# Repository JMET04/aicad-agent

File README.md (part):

# aicad-agent 1.18.0

> 当前1.18.0是待审阅的发布候选，不是已发布的稳定Release。独立插件包验证与220项测试（218通过、2跳过）已通过；全仓历史项目测试仍有证据哈希与可选CAD依赖问题。不要把以下正式版本安装步骤当成已发行的证明。

一个面向 Agent 的确定性 CAD 约束、审查与修改插件。你可以直接用自然语言告诉 Codex 要画什么、参考什么、哪些尺寸必须准确；插件负责把要求转换为逐实体计划、数学约束、CAD 文件、交互修改器和可审计验证结果。

**默认不需要 API Key。** 当前 Codex Agent 负责理解任务，本地插件负责约束验证、编译、审查和宿主适配。

v1.18.0新增[整套成本与可用性采购前检查](agent-plugin/aicad-agent/docs/PROCUREMENT_PREFLIGHT.md)：免费裸PCB不等于整套免费，完整成本/供货/功能证据/明确预算未闭合时不能推进制造；检查通过也不是采购或实机授权。见[事故复盘与电脑复查结果](docs/procurement-incident-20261009.md)。

## 产品介绍

`aicad-agent` 是安装在 Codex 中的本地工程流水线：它先冻结领域、交付阶段、标准和输入权威顺序，再生成带稳定 ID、用途、依赖和数学约束的 CAD/EDA 候选，最后交付可点击修改器、中文审计、机器验证和 SHA-256 文件清单。它面向需要“可编辑、可复核、可追溯”结果的设计与工程流程，而不是只输出一张看起来相似的图片。

产品覆盖通用 2D、建筑制图、包装刀版、参考图重建、受控 SolidWorks 3D，以及机械技术包和 PCB 证据合同检查。没有原生宿主或专业证据时会明确降级，绝不把候选一致性冒充制造、施工或投板授权。

统一入口显式覆盖机械、电子/电气、包装、土木、建筑和钢结构，并按对象需要提供 2D、3D 与交互审查；但各领域成熟度并不相同。通用制图、包装和建筑可进入受约束生成与审查，机械与 PCB 可形成哈希闭合的制造候选，土木当前仅接受权威来源绑定的受约束审查候选，钢结构当前仅提供诊断与构件关系审查。“覆盖”不等于生产级自动设计，任何施工、结构计算、加工或投板结论仍需相应专业人员和真实工具放行。

| 快速入口 | 内容 |
|---|---|
| [完整产品介绍](docs/PRODUCT_OVERVIEW.zh-CN.md) | 适用人群、工作方式、核心模块、支持范围、交付物和安全边界 |
| [四领域工程展示](showcase/README.md) | 建筑、钢结构、机械和 PCB 的预览、交互审查与验证材料 |
| [v1.15.0 标准化重生成证据](showcase/standardized-regeneration-v1.15.0/README.md) | 新机械包与受阻电子包、预览、精确哈希和工程边界 |
| [安装和使用指南](docs/INSTALL.zh-CN.md) | Marketplace、Release ZIP、首次使用和更新流程 |
| [v1.18.0 验证候选](dist/aicad-agent-1.18.0.zip) | 待审阅插件 ZIP；不是稳定Release |

> 当前定位是工程候选与人工审核工具。所有交付继续保持 `reviewOnly=true`、`accepted=false`、`ruleEnabled=false`、`packagingGated=true`。通过插件门禁不等于材料试验、刀模公差、量产可制造性或负责工程师技术验收。

## 四领域工程展示

[进入建筑平面、三层钢结构、复杂机械零件和四层工业控制器 PCB 的完整展示页](showcase/README.md)。每个样例都包含白底预览、交互审核页、中文与机器验证报告，以及经过脱敏和双向哈希闭包校验的确定性审核候选 ZIP。

展示通过只代表相应审核门禁和证据闭包成立；机械样例不自动取得制造验收，PCB 样例在缺少原生 ERC/DRC、SPICE 或仍有未路由网络时继续保持 `fabricationReady=false`。

v1.15.0 的[标准化重生成证据](showcase/standardized-regeneration-v1.15.0/README.md)取代旧机械/电子图纸作为当前工程审查候选：机械证据闭包通过但不等于技术包或制造批准；电子包的原生 ERC 与几何 DRC 均为 0，但仍有 37 个未连接项，因此 Gerber、钻孔和 job 文件被有意扣留。

## 自动打开审查界面

`generate`、`compile`、`build3d` 和 `multiview` 会生成绑定当前源哈希的审查 HTML 和打开记录；CLI/Agent 默认 `review_launch=never`，不会反复新建浏览器标签。显式使用 `auto` 时，HTML 会先复制到持久内容寻址目录并在 300 秒窗口内对相同内容去重；只有 `always` 才强制再次打开。临时源文件删除后，已打开页面仍有效；打开界面不等于接受设计。

普通“打开/看看/预览”请求必须调用 `aicad_open_review_request`，并且只打开通过 `aicad_selectable_vector_modifier_v1` 的当前交互修改器：真实 `cad-view` SVG、独立宽 `view-hit`、源对象/子对象 ID、图层、语义目录、模型测量和受控纠错缺一不可；单有 `data-artifact-role` 标签的 PDF/图片浏览器必须失败关闭。栅格内容只能作为已声明的次要底图。即使参数中有 PDF、DWG、STEP 或 KiCad 路径，也不得直接打开。只有用户明确要求原生 CAD 编辑或输出时才设置 `open_native_cad=true`，而且修改器必须先成功打开，否则原生 CAD 被阻断。

## 30 秒了解它能做什么

| 能力 | 用户看到的结果 | 插件内部保证 |
|---|---|---|
| 跨领域规范预检 | 明确领域、交付阶段、适用标准和规则包 | 规范治理是阶段 0 非补偿门禁；标准与批准工程输入优先于偏好、参考 CAD、图片和推测 |
| 自然语言画 2D CAD | DXF、SCR、AICAD、审计和清单 | 每条线都有 ID、用途、推理、依赖和数学约束 |
| 建筑平面专业制图 | 剖切粗实线、投影中实线、隐藏虚线、数学绑定轴网、原生尺寸 | 自动校验轴线坐标/覆盖、两端轴圈相切、轴号同值居中、房间用途来源、逐房间设备、全占用体净空、语义线宽线型、DIMSTYLE 与修改器显示一致性 |
| 规范报告质量 | 完整现象/根因/修正/预防规则记录、稳定唯一规则 ID | 相同记录折叠、冲突 ID 失败、同输入重复运行哈希一致 |
| 包装刀版设计与复核 | 切割/压痕/开槽/胶区分层图、白底预览、对象编号 | 先核对整体结构，再检查轮廓、闭合、槽口、胶区、公式和参数域 |
| 点击修改 2D/3D | 点线看长度和端点，点点看 XYZ，点圆看半径/直径/圆心 | 数值来自编译模型，不来自屏幕像素 |
| 多对象关系修改 | 选择两条线后直接提供平行、垂直、共线、等长等选项 | 修改绑定源对象、保留策略和依赖重放 |
| 坐标系与多视图 | 一个开关同步隐藏/显示二维轴、原点和三维轴 | 统一使用右手 `MODEL_XYZ`，单位为 mm |
| 网页/图片/PDF 参考重建 | 可编辑的 1:1 CAD、标注、文字和预览 | 图片只提供外观/拓扑；尺寸必须来自权威数据或校准关系 |
| AutoCAD 适配 | SCR/DXF、bundle、AICAD XData；有宿主时可生成 DWG | DWG、XData 和保存重开必须由真实 AutoCAD 门禁证明 |
| SolidWorks 3D | 受控拉伸、切除、孔阵列、SLDPRT/STEP | 事务式执行、重建回读、可选原生持久拓扑验证 |
| 错误学习闭环 | 报告“现象—根因—修复—新增规则” | 每个新错误必须加入永久规则和可重复回归测试 |

## 为什么不是“直接让 AI 发 CAD 命令”

直接拼接 CAD 命令很容易出现三类低级错误：中文进入命令流导致乱码；局部线段看似正确但整体产品结构错误；同类错误每次依赖人工重新发现。

`aicad-agent` 使用不可跳过的四级门禁。规范不是最终润色项，而是任何几何生成之前的阶段 0：

```mermaid
flowchart LR
  A["用户要求与权威输入"] --> N["0. 领域、阶段、标准与规则包"]
  N -->|PASS| B["1. 整体要求一致性"]
  B -->|PASS| C["2. 逐实体与数学可靠性"]
  C -->|PASS| D["3. 隔离构建与哈希审计"]
  D --> E["CAD + 修改器 + 审计 + 验证"]
  N -->|FAIL| X["阻断后续输出"]
  B -->|FAIL| X
  C -->|FAIL| X
```

规范门禁要求声明 `domain`、`deliveryStage`、`applicableStandards`、`selectedRulePacks` 和输入权威顺序；任何高优先级规则都必须同时落到 schema/contract 字段、生成约束、独立 QA 与负向回归测试。整体门禁要求每条硬需求满足 `boundActual = observed = expected`；几何门禁计算独立约束秩并检查拓扑、功能面和参数域；构建门禁在隔离目录核对文件身份、ASCII 执行通道和 SHA-256。复制一个“正确数字”到报告里不能绕过验证。

## 安装步骤

### 方式 A：从 GitHub marketplace 安装（推荐）

准备：Codex CLI 或 Codex 桌面版、Git、Python 3.10+。

```powershell
codex plugin marketplace add JMET04/aicad-agent --ref v1.18.0
codex plugin add aicad-agent@aicad-agent
codex plugin list
```

看到 `aicad-agent` 为 `installed, enabled` 后，**新建一个 Codex 任务**。插件技能和 MCP 工具会在新任务的干净上下文中加载。

更新：

```powershell
codex plugin marketplace upgrade aicad-agent
codex plugin add aicad-agent@aicad-agent
```

卸载：

```powershell
codex plugin remove aicad-agent
```

### 方式 B：下载压缩包

从 [GitHub Releases](https://github.com/JMET04/aicad-agent/releases) 或仓库的 [`dist`](dist/) 目录下载：

- `aicad-agent-1.18.0.zip`
- `SHA256SUMS`

先核对哈希：

```powershell
Get-FileHash .\aicad-agent-1.18.0.zip -Algorithm SHA256
Get-Content .\SHA256SUMS
```

解压后顶层目录为 `aicad-agent`，其中包含插件清单、技能、MCP、规则、Schema、脚本、测试、AutoCAD bundle 源和 SolidWorks 宿主源。

## 第一次使用：完全不需要写代码

### 第 1 步：把目标和权威尺寸说清楚

在新 Codex 任务中直接输入，例如：

> 使用 aicad-agent 画一个 120×80×12 mm 的安装板，中心开直径 30 mm 的通孔。第一条生产线从原点开始，每个实体写明用途、依赖和数学约束。先核对整体要求，再输出 DXF、AICAD、审计、验证和多视图修改器。

如果有参考图纸、网页截图、PDF、DXF 或产品数据，直接附上并说明优先级。推荐写法：

> 尺寸以 design.json 为最高优先级，DXF 用于几何对象对应，图片只用于外观和标注布局，不允许从像素猜尺寸。

### 第 2 步：让 Agent 先做整体核验

插件应先确认：

1. 产品类型和用途是否匹配；
2. 结构族、标准、上部/下部闭合是否匹配；
3. 关键尺寸由哪个输入提供权威；
4. 必需、允许和禁止的功能；
5. 需要输出哪些 CAD、预览、审计和验证文件；
6. 是否存在输入冲突或未经确认的高影响假设。

整体要求没有证明一致时，不应先画一堆线再返工。

### 第 3 步：查看生成结果

基础 2D 编译通常会得到：

- `*.plan.json`：规范化意图计划；
- `*.aicad`：ASCII 约束执行记录；
- `*.scr`：AutoCAD 脚本；
- `*.dxf`：便携二维几何；
- `*.audit.md`：中文逐实体用途、关系、根因和审计；
- `*.manifest.json`：版本、实体统计、源计划身份和文件哈希。

包装或参考重建任务还可生成白底 PNG、原生中文 SVG、交互 HTML、对象目录、`validation.json` 和 `validation.md`。

### 第 4 步：用修改器审查和修改

对 Agent 说：

> 用 aicad-agent 打开这次结果的多视图修改器，我要逐项检查和修改。

在修改器中：

1. **点击直线**：右侧“几何数值”显示模型长度、起点 XYZ、终点 XYZ；可编辑长度会自动回填正确控制参数。
2. **点击点**：显示该点在 `MODEL_XYZ` 中的 X/Y/Z 坐标；参数化中心点可直接回填中心坐标。
3. **点击圆**：显示半径、直径和圆心 XYZ；点击半径可回填对应半径参数。
4. **点击面**：显示模型面积和几何中心；面仍作为审查对象，不冒充原生宿主 BREP 名称。
5. **坐标系开关**：顶部“坐标系”开关同步控制所有二维/截面视图的轴和原点，以及可旋转三维视图的 XYZ 三轴。
6. **多选关系**：连续选择两个兼容对象，直接选择平行、垂直、共线、等长、同心、重合等可用关系。
7. **文字修改**：也可以直接描述“让这两条线共线，孔径改成 18 mm，其他关键尺寸保持不变”。
8. **自由截面**：三维任务可使用轴向截面或 `法向量 + 经过点` 定义任意截面，并把截面曲线映射回语义参数。

修改器记录的是受控修改请求。“复制并回传给 AI”会同时复制 JSON、发送浏览器/WebView 回传事件；Agent 必须先校验 handoff schema 与当前源 SHA-256，再预览、应用、写审计并重新生成可点选修改器。旧源、纯文字且无精确事务或约束失败都会在写文件前阻断，不能用一次点击绕过整体结构检查。

### 第 5 步：要求最终复核

推荐直接说：

> 对最终结果做整体核验：逐项比对用户要求、权威尺寸、对象目录、几何、图层、标注、文字编码、视觉重叠、宿主重开和文件哈希。发现错误时同时给出根因和需要新增的永久规则。

只有有真实 AutoCAD/SolidWorks 宿主证据的项目，才能报告对应宿主保存重开通过。

## 常用任务提示词

### 普通 2D

> 使用 aicad-agent 绘制一块 200×120 mm 的板，四角 R10，中心孔直径 24 mm。尺寸以我提供的数值为准；逐实体解释用途和约束，验证后输出 DXF、SCR、审计和修改器。

### 包装刀版

> 使用 aicad-agent 设计插舌上盖、自锁底的包装展开图。先确认整体结构族和上下闭合，不允许上下镜像猜测；检查每个摇盖、插舌、槽口、胶区、闭合公式和参数组合，通过后再输出分层 CAD 和白底中文审查图。

### 网页或图片参考图

> 使用 aicad-agent 按参考网页重建 1:1 CAD。尺寸以页面标注和我给的校准尺寸为准；图片像素不能作为尺寸真值。保持结构比例、文字、标注位置、旋转、线宽层级，并检查乱码和重叠。

### 受控 3D

> 使用 aicad-agent 建一个 120×80×12 mm 安装板，中心凸台直径 30 mm、高 8 mm，中心通孔直径 15 mm。先生成受控 3D 计划和多视图修改器；如果本机 SolidWorks 可用，再生成 SLDPRT/STEP 并保存重开验证。

## 主要功能详解

### 1. 2D 逐实体约束

支持 `LINE`、`CIRCLE`、`ARC`。每个实体必须包含稳定 ASCII ID、用途、推理、已生成依赖、数学约束、图层和生产语义。首实体锚定 `(0,0)`，禁止前向引用、零长度、非正半径和重复几何；必要时可使用不会进入生产输出的 `ORIGIN_BOOTSTRAP`。

### 2. 数学确定性与产品正常性

插件不是简单统计“写了多少条约束”，而是计算独立雅可比秩。等式满秩只证明几何唯一，不证明产品正确，所以还会检查单闭合轮廓、端点归属、结构面、功能面、工艺区、上下闭合、结构公式和参数组合。

### 3. 包装刀版规则

当前规则覆盖切割/压痕/开槽/胶区语义、端点连续、轮廓简单性、圆角切线、槽宽、摇盖对口、插舌完整面与锥度、胶区、闭合公式、外包框、上下闭合分型和耦合参数域。默认模板是已建模回归结构，不会把“常见结构”当成所有包装的默认真值。

### 4. 精确选择与关系修改

可见细线和点击命中区分离，既保持图纸精细，又让线段容易点中。对象使用稳定语义键跨视图同步；边号、角号、面号可保留；修改事务绑定源哈希、保留策略、共享阵列影响范围和完整依赖重放。

### 5. 模型测量与坐标系

每个可选线、点、圆、面都携带类型化 `measurement`。长度、端点、坐标、半径、直径、面积和中心来自约束求解后的模型。屏幕缩放、透视投影和命中像素没有尺寸权威。统一坐标系是右手 `MODEL_XYZ`，单位为 mm。

### 6. 1:1 参考重建

支持校准网页 SVG、SVG、光栅图和 PDF。矢量对象可按真实 DOM/object ID 映射；光栅图必须由权威尺寸或校准点建立比例。几何、尺寸、文字内容、标注位置/旋转、线宽、比例、乱码和重叠分别设门禁。

### 7. AutoCAD

无 AutoCAD 时仍可生成 AICAD、SCR、DXF、审计和清单。安装 AutoCAD 2025+ 后，可通过 bundle 执行、保存 DWG、写入 AICAD XData，并在保存重开后复核图层、坐标、中文和 XData。便携 DXF 不能冒充 DWG 宿主验证。

### 8. SolidWorks 3D

受控特征集包括基础拉伸、凸台拉伸、切除、中心矩形、圆和圆周阵列。无宿主时可以 `--no-execute` 生成计划与审计；有已授权 SolidWorks 2026 时可构建 SLDPRT/STEP、回读实体/体积/面积/包围框，并验证持久拓扑引用。未支持的特征会明确拒绝，不会静默近似。

### 9. 防乱码与审计

AICAD/SCR 执行通道保持 ASCII；中文用途、推理、根因和说明进入 UTF-8 审计及 CAD TEXT/MTEXT。每个候选文件写入 SHA-256，验证源计划身份和必需工件完整性。

### 10. 错误学习

发现错误后必须记录 `symptom`、`root cause`、`correction`、`prevention rule`、永久规则 ID 和可稳定重现旧错误的回归样例。这样错误会在后续任务中被自动阻断，而不是每次重新画很多遍。

## MCP 工具

插件公开 9 个本地 MCP 工具：

- 通用：`aicad_capabilities`；
- 2D：`aicad_get_plan_schema`、`aicad_generate`、`aicad_validate_plan`、`aicad_compile_plan`；
- 3D：`aicad_solidworks_doctor`、`aicad_get_3d_plan_schema`、`aicad_validate_3d_plan`、`aicad_build_solidworks_part`。

## 本地 CLI 使用

克隆仓库并查看能力：

```powershell
git clone https://github.com/JMET04/aicad-agent.git
cd aicad-agent
python agent-plugin/aicad-agent/scripts/aicad_agent.py capabilities
```

编译示例 2D 计划：

```powershell
python agent-plugin/aicad-agent/scripts/aicad_agent.py compile `
  --plan examples/rectangle.plan.json `
  --out build/rectangle `
  --name rectangle
```

生成 3D 计划但不调用 SolidWorks：

```powershell
python agent-plugin/aicad-agent/scripts/aicad_agent.py build3d `
  --plan examples/mounting_plate_3d.plan.json `
  --out build/mounting-plate `
  --name mounting_plate `
  --no-execute
```

包装任务的受控输出边界：

```powershell
python agent-plugin/aicad-agent/scripts/aicad_guarded_delivery.py `
  --contract requirement-contract.json `
  --trace requirement-trace.json `
  --plan drawing.plan.json `
  --geometry geometry.json `
  --template structure.normality.json `
  --instance drawing.instance.json `
  --out build/candidate `
  --report-dir build/reports `
  --name drawing
```

## 依赖与降级行为

| 环境 | 可用能力 | 明确不可声称 |
|---|---|---|
| Python 3.10+ 标准库 | 基础 2D 计划验证与编译 | 包装拓扑/预览依赖未安装时的完整 QA |
| 加装 `jsonschema`、`ezdxf`、`Pillow`、`Shapely` | 合同、DXF、预览、包装拓扑 QA | AutoCAD/SolidWorks 原生宿主结果 |
| AutoCAD 2025+ | DWG、XData、保存重开门禁 | 材料或量产验收 |
| SolidWorks 2026 + .NET Framework 4.8 | SLDPRT、STEP、原生拓扑重开 | 未建模特征族的正确性 |

安装可选包装依赖：

```powershell
python -m pip install -r agent-plugin/aicad-agent/requirements-packaging.txt
```

默认包不分发 SolidWorks 专有互操作 DLL。

## 开发与验证

```powershell
python -B -m unittest discover -s tests -p "test_*.py" -v
python -B -m unittest discover -s agent-plugin/aicad-agent/tests -p "test_*.py" -v
.\scripts\build-agent-plugin.ps1 -OutputDirectory release/ci -Version 1.18.0
python -B scripts/verify_release_package.py release/ci/aicad-agent --source-root .
.\scripts\build-github-source.ps1 `
  -OutputDirectory release/ci/github-repository `
  -Version 1.18.0 `
  -PluginArchive release/ci/aicad-agent-1.18.0.zip `
  -PluginDirectory release/ci/aicad-agent
python -B scripts/verify_github_source.py release/ci/github-repository --source-root .
```

当前 1.14.0 新增机械/电子生成前规范门禁：它从同一份生产规则清单派生精确的 54 条机械和 63 条电子规则，在任何 2D/3D 几何或构建产物写出前检查规则完整性、适用标准、来源绑定、冲突和安全锁。v1.13.0 的 71/99 条生成后证据门禁继续保留；两层门禁分别约束“先按规范生成”和“生成后证据闭包”，均不授予技术、制造或投板批准。

## 文档索引

- [完整产品介绍](docs/PRODUCT_OVERVIEW.zh-CN.md)
- [详细功能说明](docs/FUNCTIONS.zh-CN.md)
- [安装和使用指南](docs/INSTALL.zh-CN.md)
- [选择测量与坐标系契约](docs/SELECTION_MEASUREMENT_UI_V3.md)
- [CAD 修改器交互契约](docs/MODIFIER_UI_V2.md)
- [精确子对象修改](docs/EXACT_SUBOBJECT_CORRECTION.md)
- [网页/图片参考重建](docs/WEB_REFERENCE_REBUILD.md)
- [SolidWorks 原生拓扑回读](docs/NATIVE_SOLIDWORKS_TOPOLOGY.md)
- [变更日志](CHANGELOG.md)
- [安全策略](SECURITY.md)
- [第三方依赖说明](THIRD_PARTY_NOTICES.md)

## v1.14.0 技术说明

以下两节保留机械、PCB 与持续学习门禁的精确定义；面向用户的中文说明请优先阅读[完整产品介绍](docs/PRODUCT_OVERVIEW.zh-CN.md)和[发布说明](docs/RELEASE_NOTES_v1.18.0.md)。

## Mechanical/electronics normative generation preflight

Mechanical and electronics work now has a real pre-geometry gate, not only a post-generation evidence checklist. The gate derives one exact inventory from `production_readiness_rules.json`: 54 mechanical generation rules and 63 electronics generation rules, including seven shared authority/detail/drafting/sheet/discipline/non-compensation rules. Missing, extra, duplicate, unresolved, reference-only or unauthorized `not_applicable` rows block 2D validation/compilation and 3D validation/SolidWorks build before artifacts are written.

Use the MCP tools `aicad_get_engineering_preflight_schema`, `aicad_get_engineering_preflight_template` and `aicad_validate_engineering_preflight`, then embed the pass in the plan as `engineering_normative_preflight`. The CLI equivalent is `scripts/aicad_engineering_preflight.py`. See [the complete preflight contract and coverage](docs/ENGINEERING_NORMATIVE_PREFLIGHT.md).

A preflight pass means only that controlled generation may start. It does not expose artifacts or grant technical, manufacturing, fabrication or release readiness. The post-generation v3 evidence contract remains mandatory.

## 机械与 PCB 证据合同门禁

The canonical v3 QA is deliberately narrower than a readiness assessor. It verifies that declared mechanical or PCB evidence satisfies the rule inventory, uses portable hash-correct artifacts, and has an exact bijection between `expectedArtifactClosure` and `candidateArtifacts`. Repeated artifact kinds are supported through unique `artifactId`, `partId`, revision and case-insensitive path identity, so multi-part assemblies and granular CAM do not have to be hidden in one archive. It does not authenticate evidence origin, replay native CAD/EDA tools, independently reproduce engineering analyses, expose candidate artifacts, or grant technical/manufacturing/fabrication readiness.

Mechanical gates cover frozen operating envelope, duty cycle, design life, load combinations and abnormal cases; equation/input/output/margin trace; strength, stiffness, fatigue, factors of safety, fasteners, joints, bearings and thermal behavior; risk controls; fits, threads, undefined edges, GD&T, roughness, process capability and measurement method; native material-database assignment; revision/BOM/inspection parity; and feature-bound drawing annotations. Every manufactured part and required assembly must contribute its own native CAD, STEP and manufacturing drawing, with artifact-ID source binding and native reopen evidence. Canonical QA parses one `aicad_machine_mechanical_bom_v1` JSON BOM: it requires one positive-quantity row per subject with exact subject type, revision and artifact IDs, then requires the hash-bound product-structure manifest to repeat those subject-scoped BOM rows exactly. PCB gates cover exact MPN-to-symbol pin number/function/type resolution; ratings, derating, power/startup/fault recovery, transient protection, analog accuracy, clocks/reset/programming, grounding/isolation, connector and test access; bidirectional net/pad and BOM/footprint parity; zero final unconnected or ignored/excluded ERC/DRC items; enclosure/height checks; and granular Gerber/drill/CAM outputs from the same revision. Every `pcb_design` must independently own its KiCad project/schematic/board, schematic PDF, BOM, CPL, assembly drawing, fabrication drawing, 3D board, job file, CAM manifest and all Gerber/PTH/NPTH drill outputs; one package-level document cannot stand in for another PCB. Canonical QA parses each final `.kicad_pcb` S-expression to derive its copper-layer set and PTH/NPTH presence; the candidate board inventory must match that parse, and the CAM manifest must close every named Gerber layer, typed drill output and job artifact ID/hash in both directions. These checks establish candidate-declared consistency only, not external source authority or evidence authenticity.

Artifact-set SHA-256 binds each artifact ID, part ID, subject type, kind, revision, normalized relative path, byte size and content hash. Artifact IDs and case-folded paths must be unique; kinds may repeat. Rule-owned predicates and source-artifact selectors require complete artifact-ID/hash maps and cannot be replaced by one hash per kind. Required standards are checked as a minimum subset so project-specific standards remain permitted.

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
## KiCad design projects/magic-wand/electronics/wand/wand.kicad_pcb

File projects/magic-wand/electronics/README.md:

# Magic Wand Electronics Package — EVT Review Only

> **BLOCKED NATIVE OUTPUTS:** `kicad-cli`, `ngspice`, and `arm-none-eabi-gcc` were not found on PATH or in the checked common installation paths on 2026-08-21. No KiCad schematic/PCB was synthesized, no ERC/DRC or SPICE analysis was run, no Gerber/drill/BOM/CPL was exported, and no embedded binary was compiled. The CSV connectivity tables and JSON constraints in this directory are the review source of truth until a qualified engineer captures them in KiCad and closes the gates in `review-report.md`.

Status: **EVT review-only; not certified, not production-authorized, and not approved for safety-critical actuation.**

This package defines two low-voltage prototypes:

- a battery wand using NINA-B302-00B-00, LSM6DSV16X, BQ25185, TPS63900 and DRV2605L; and
- a USB-powered receiver using NINA-B302-00B-00 with 3.3/5 V-referenced UART/PWM, one signal-isolated open-collector output, and one common-ground 5–12 V low-side MOSFET output.

The receiver contains **no mains circuitry** and **no flight-power stage**. Mains loads require an external, appropriately certified relay/contactor product. Flight controllers may connect only through UART, SBUS/CRSF-over-UART, PWM/AUX signal interfaces; propulsion, ESC battery and motor wiring stay outside this PCB.

## Review order

1. `review-report.md` — native-tool blockers, analyses run/not run, gates and risk.
2. `evidence-manifest.json` — primary manufacturer evidence and checked claims.
3. `system-architecture.md` and `interface-control.md` — boundaries and electrical contracts.
4. `wand/connectivity.csv` and `receiver/connectivity.csv` — source-of-truth logical connectivity.
5. `design-calculations.md`, `pcb-constraints.json`, `test-points.csv` — calculations and layout/test intent.
6. `bom.csv` and `fmea.csv` — sourcing, alternates and risk controls.
7. `bring-up-and-production-test.md` — safe staged evaluation and proposed manufacturing tests.

## Evidence status vocabulary

- **datasheet-checked**: directly supported by the cited manufacturer document.
- **design-choice**: selected by this EVT design and still requires hardware validation.
- **inferred**: engineering inference requiring independent review.
- **blocked**: cannot be demonstrated with the tools or artifacts available here.

Part numbers, footprints, land patterns, polarity, pin-one orientation, antenna clearance and assembly options must be independently checked against the exact orderable-part revision before schematic capture or procurement.

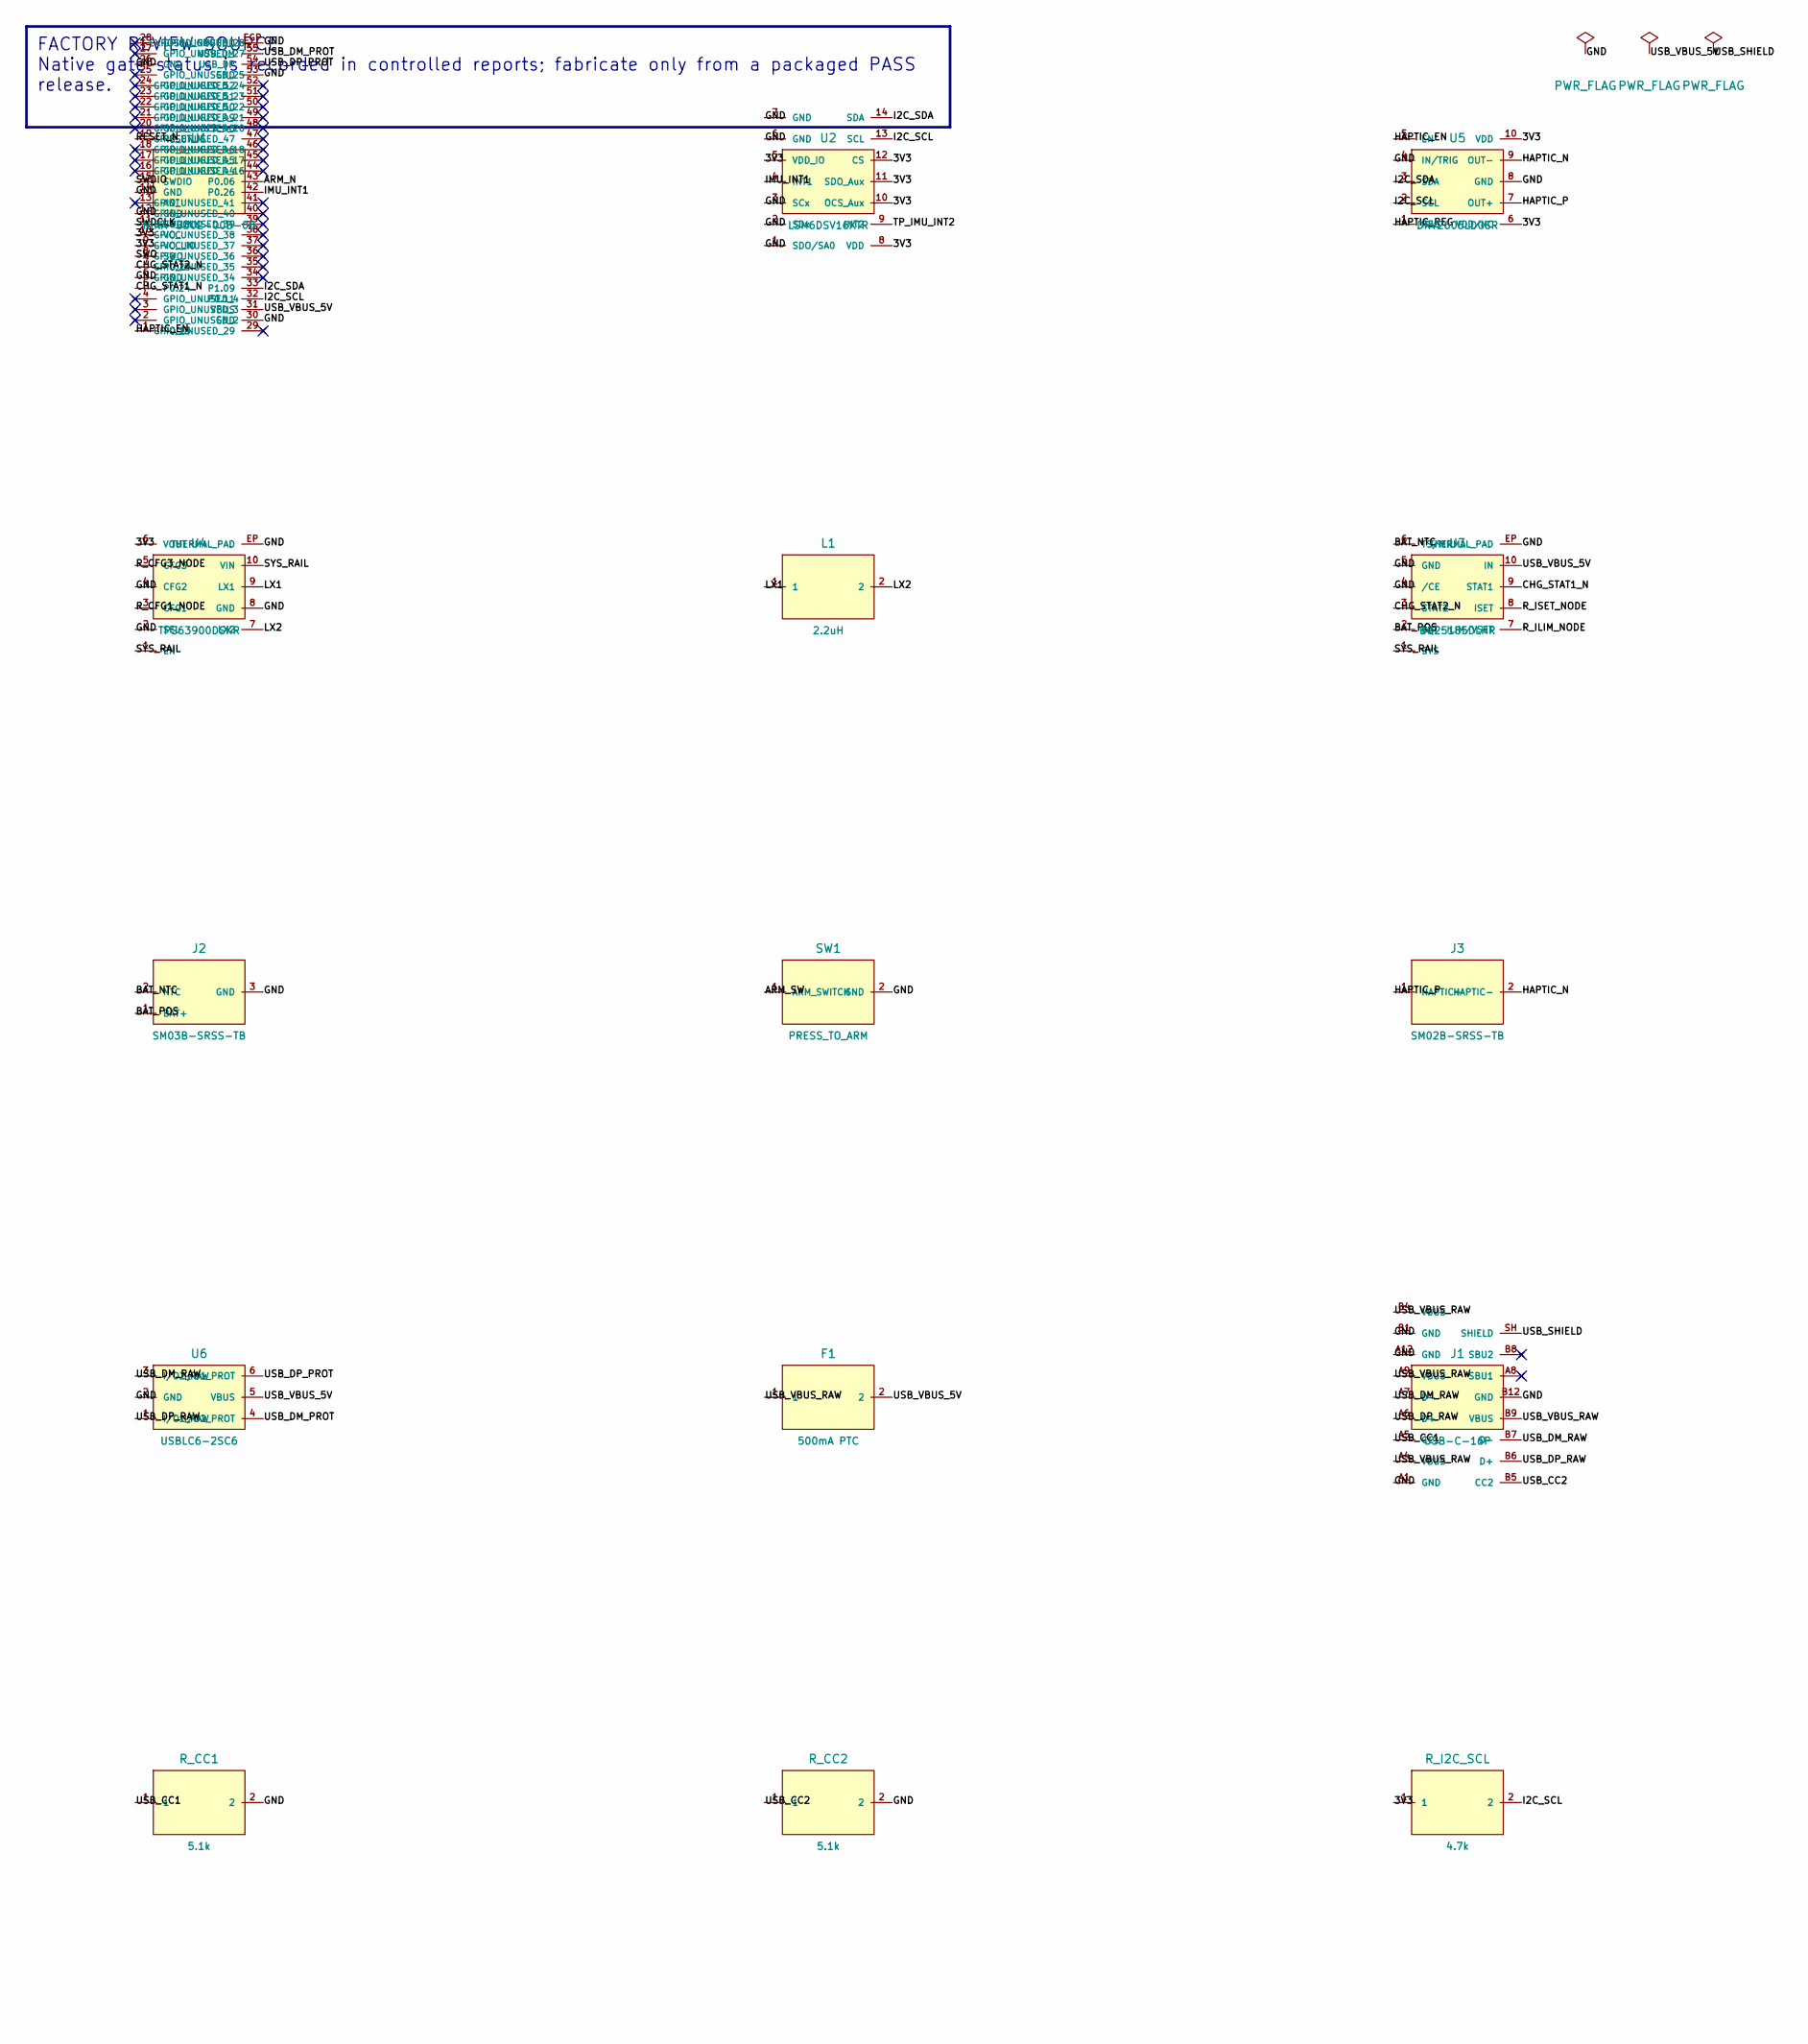
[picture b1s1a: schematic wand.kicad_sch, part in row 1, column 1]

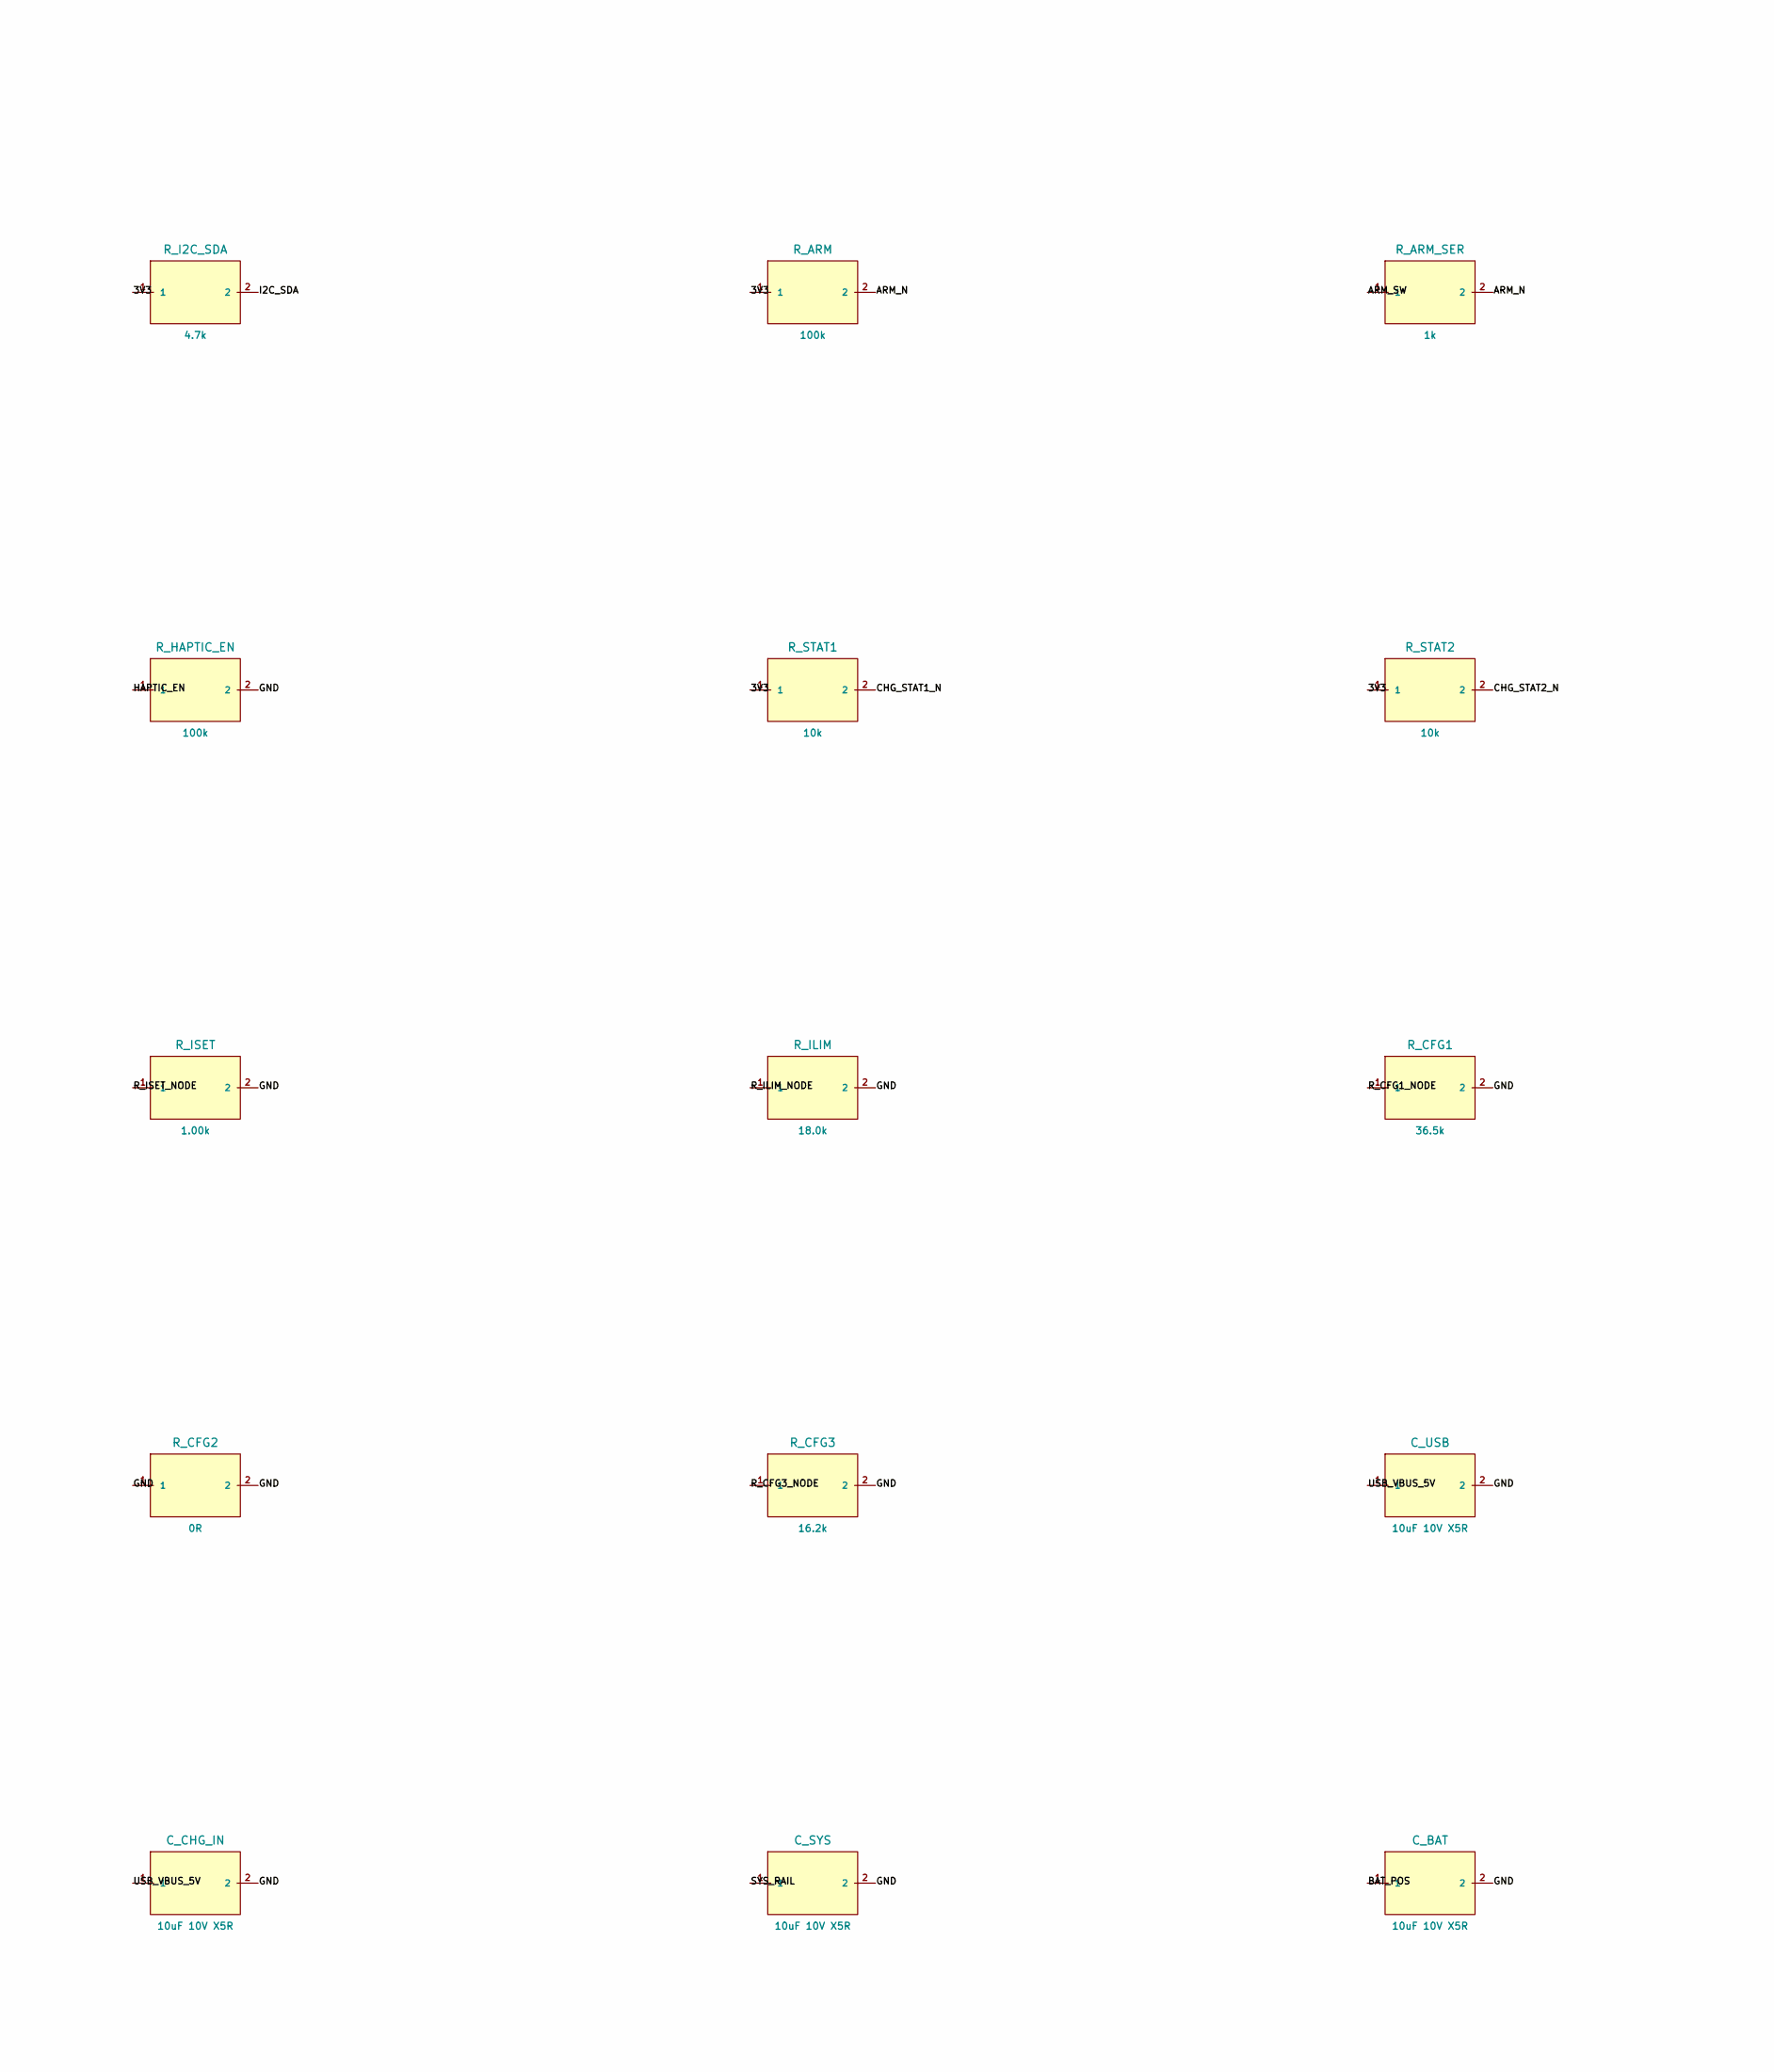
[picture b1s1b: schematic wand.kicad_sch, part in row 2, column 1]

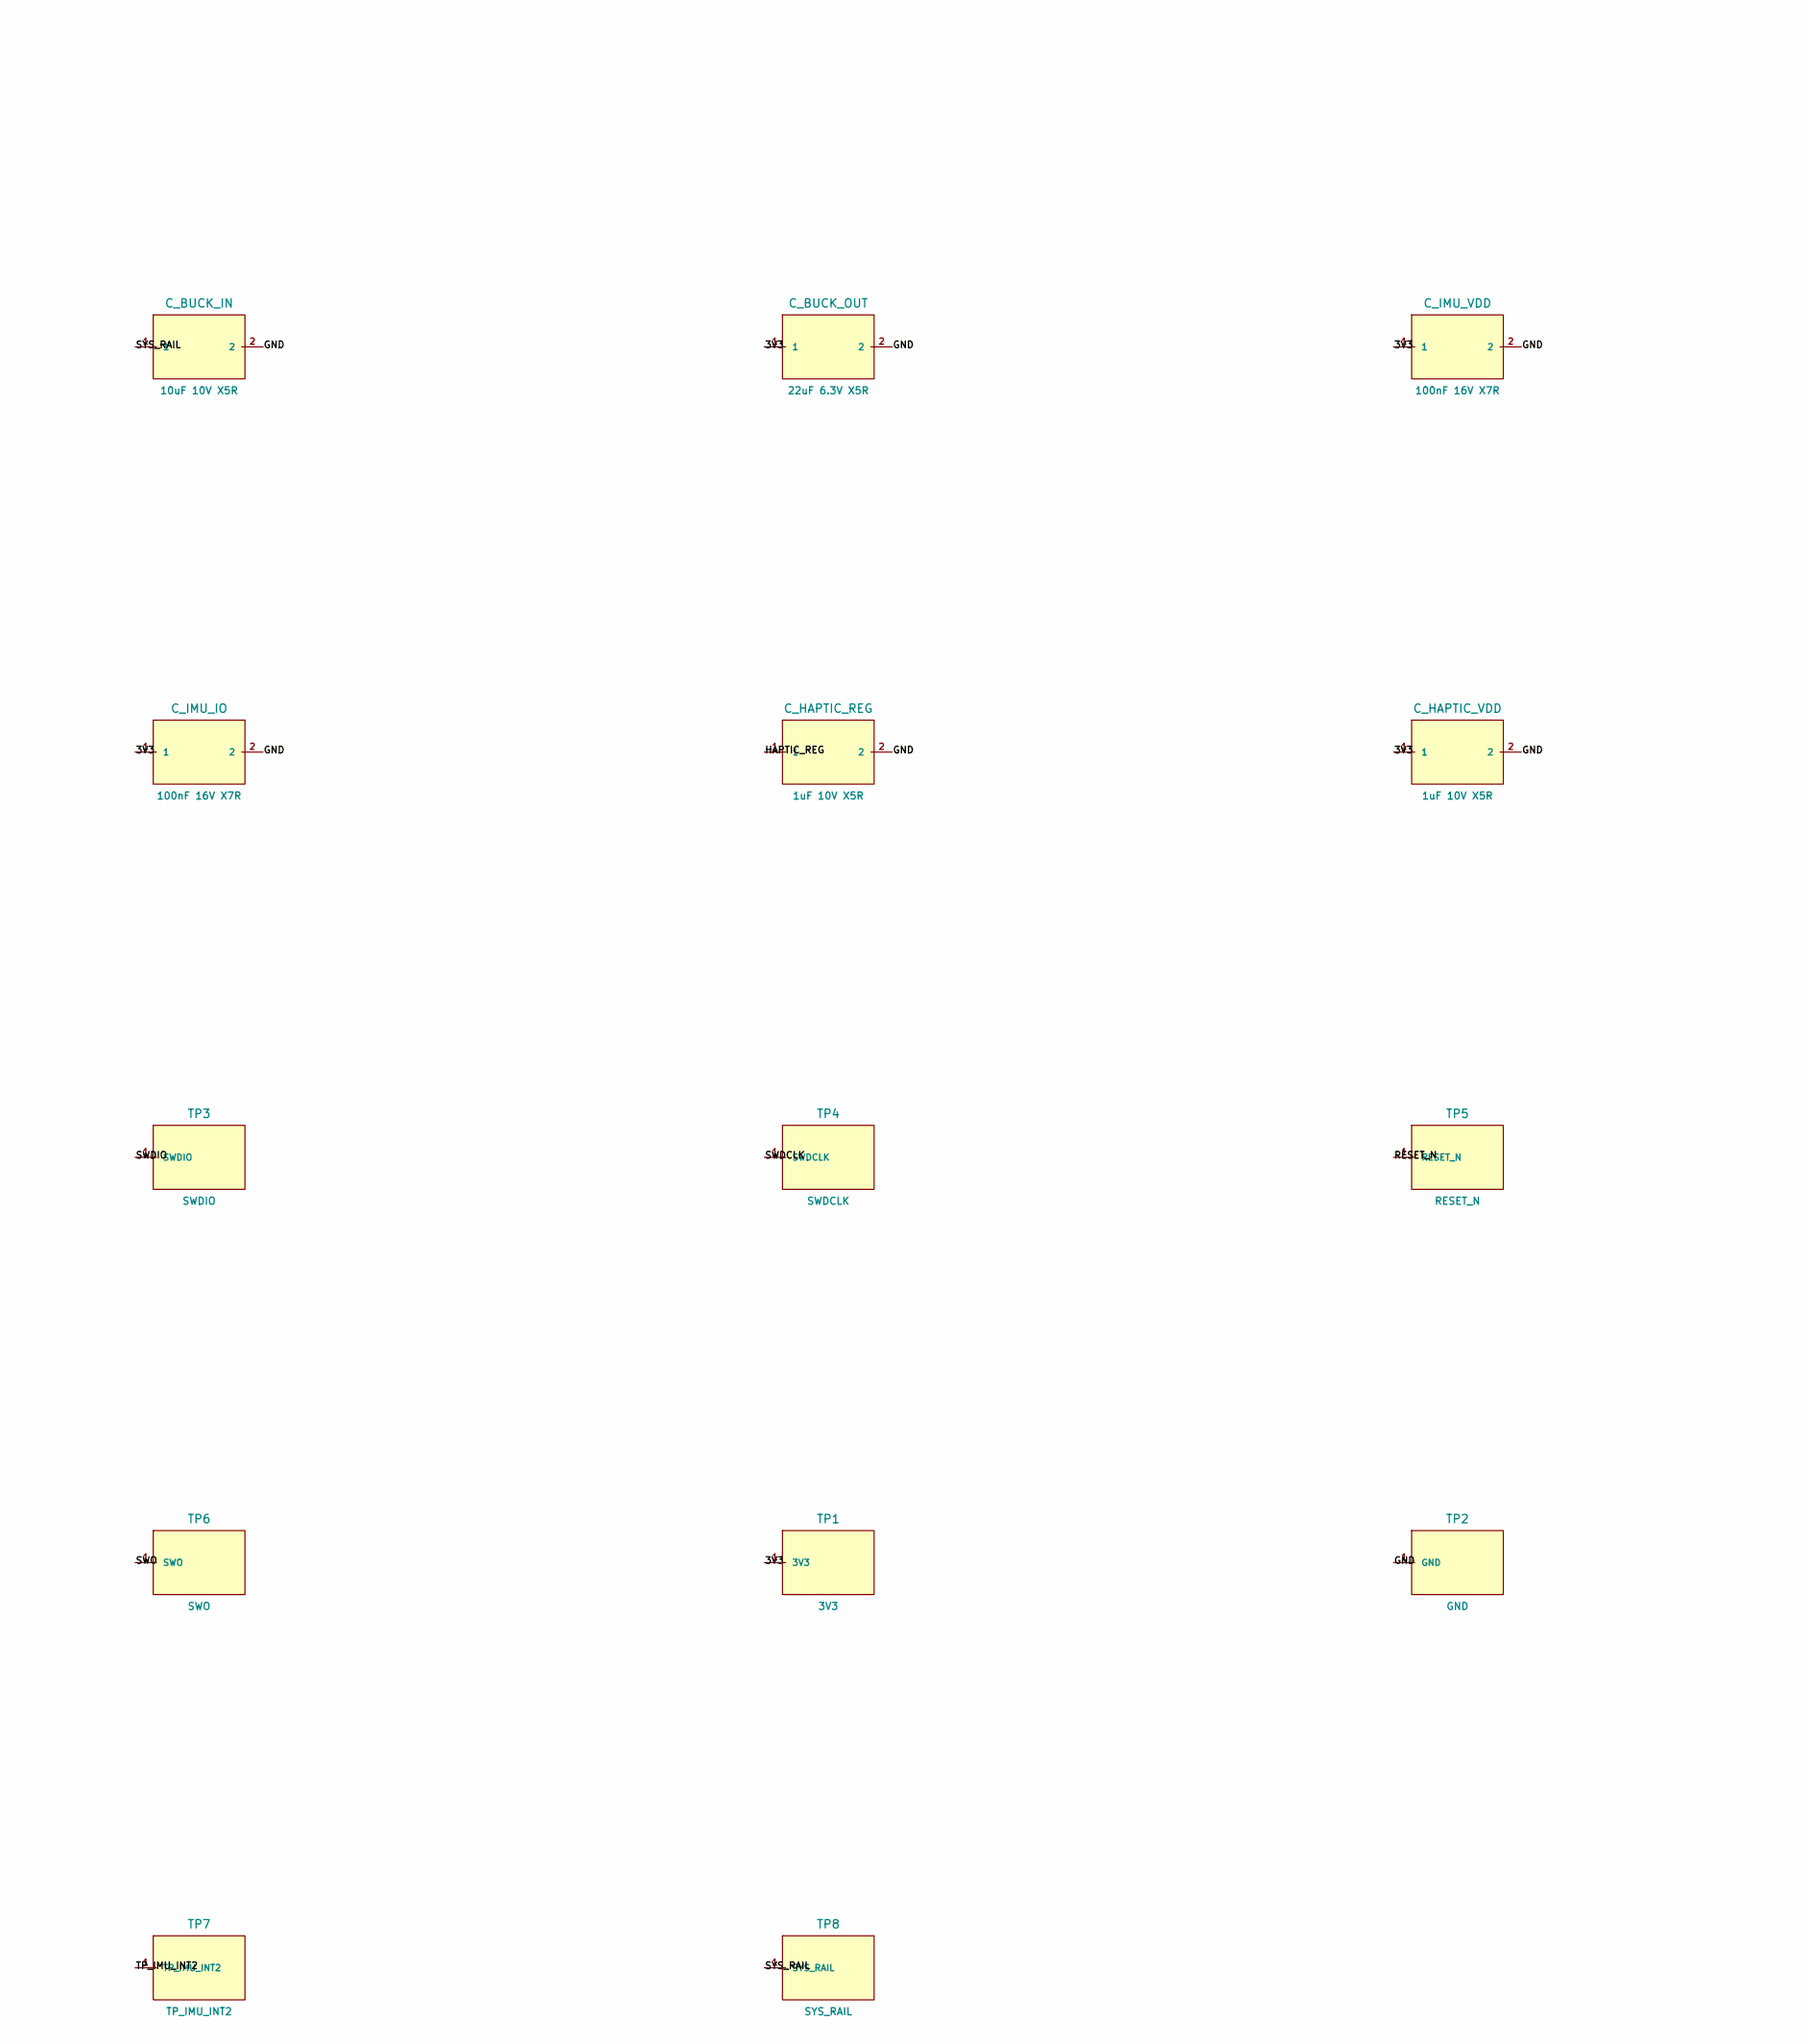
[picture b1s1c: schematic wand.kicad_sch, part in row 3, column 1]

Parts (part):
C_BAT: 10uF 10V X5R; wand_C_BAT; MPN GRM21BR61A106KE19L; LCSC C77073
C_BUCK_IN: 10uF 10V X5R; wand_C_BUCK_IN; MPN GRM21BR61A106KE19L; LCSC C77073
C_BUCK_OUT: 22uF 6.3V X5R; wand_C_BUCK_OUT; MPN GRM21BR60J226ME39L; LCSC C77071
C_CHG_IN: 10uF 10V X5R; wand_C_CHG_IN; MPN GRM21BR61A106KE19L; LCSC C77073
C_HAPTIC_REG: 1uF 10V X5R; wand_C_HAPTIC_REG; MPN CL05A105KP5NNNC; LCSC C14445
C_HAPTIC_VDD: 1uF 10V X5R; wand_C_HAPTIC_VDD; MPN CL05A105KP5NNNC; LCSC C14445
C_IMU_IO: 100nF 16V X7R; wand_C_IMU_IO; MPN GRM155R71C104KA88D; LCSC C1525
C_IMU_VDD: 100nF 16V X7R; wand_C_IMU_VDD; MPN GRM155R71C104KA88D; LCSC C1525
C_SYS: 10uF 10V X5R; wand_C_SYS; MPN GRM21BR61A106KE19L; LCSC C77073
C_USB: 10uF 10V X5R; wand_C_USB; MPN GRM21BR61A106KE19L; LCSC C77073
F1: 500mA PTC; wand_F1; MPN MF-FSMF050X-2; LCSC C210357
J1: USB-C-16P; wand_J1; MPN DX07S016JA1R1500; LCSC C3197885
J2: SM03B-SRSS-TB; wand_J2; MPN SM03B-SRSS-TB(LF)(SN); LCSC C160403
J3: SM02B-SRSS-TB; wand_J3; MPN SM02B-SRSS-TB(LF)(SN); LCSC C160402
L1: 2.2uH; wand_L1; MPN XFL4020-222MEC; LCSC C122469
R_ARM: 100k; wand_R_ARM; MPN RC0402FR-07100KL; LCSC C25741
R_ARM_SER: 1k; wand_R_ARM_SER; MPN RC0402FR-071KL; LCSC C106235
R_CC1: 5.1k; wand_R_CC1; MPN RC0402FR-075K1L; LCSC C25905
R_CC2: 5.1k; wand_R_CC2; MPN RC0402FR-075K1L; LCSC C25905
R_CFG1: 36.5k; wand_R_CFG1; MPN RC0402FR-0736K5L; LCSC C15011
R_CFG2: 0R; wand_R_CFG2; MPN RC0402JR-070RL; LCSC C17168
R_CFG3: 16.2k; wand_R_CFG3; MPN RC0402FR-0716K2L; LCSC C138050
R_HAPTIC_EN: 100k; wand_R_HAPTIC_EN; MPN RC0402FR-07100KL; LCSC C25741
R_I2C_SCL: 4.7k; wand_R_I2C_SCL; MPN RC0402FR-074K7L; LCSC C105871
R_I2C_SDA: 4.7k; wand_R_I2C_SDA; MPN RC0402FR-074K7L; LCSC C105871
R_ILIM: 18.0k; wand_R_ILIM; MPN RC0402FR-0718KL; LCSC C138044
R_ISET: 1.00k; wand_R_ISET; MPN RC0402FR-071KL; LCSC C106235
R_STAT1: 10k; wand_R_STAT1; MPN RC0402FR-0710KL; LCSC C25744
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
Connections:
3V3: C_BUCK_OUT.1, C_HAPTIC_VDD.1, C_IMU_IO.1, C_IMU_VDD.1, R_ARM.1, R_I2C_SCL.1, R_I2C_SDA.1, R_STAT1.1, R_STAT2.1, TP1.1 (3V3), U1.9 (VCC_IO), U1.10 (VCC), U2.5 (VDD_IO), U2.8 (VDD), U2.10 (OCS_Aux), U2.11 (SDO_Aux), U2.12 (CS), U4.6 (VOUT), U5.6 (VDD/NC), U5.10 (VDD)
ARM_N: R_ARM.2, R_ARM_SER.2, U1.43 (P0.06)
ARM_SW: R_ARM_SER.1, SW1.1 (ARM_SWITCH)
BAT_NTC: J2.2 (NTC), U3.6 (TS/MR)
BAT_POS: C_BAT.1, J2.1 (BAT+), U3.2 (BAT)
CHG_STAT1_N: R_STAT1.2, U1.5 (P0.24), U3.9 (STAT1)
CHG_STAT2_N: R_STAT2.2, U1.7 (P0.25), U3.3 (STAT2)
GND: C_BAT.2, C_BUCK_IN.2, C_BUCK_OUT.2, C_CHG_IN.2, C_HAPTIC_REG.2, C_HAPTIC_VDD.2, C_IMU_IO.2, C_IMU_VDD.2, C_SYS.2, C_USB.2, J1.A1 (GND), J1.A12 (GND), J1.B1 (GND), J1.B12 (GND), J2.3 (GND), R_CC1.2, R_CC2.2, R_CFG1.2, R_CFG2.1, R_CFG2.2, R_CFG3.2, R_HAPTIC_EN.2, R_ILIM.2, R_ISET.2, SW1.2 (GND), TP2.1 (GND), U1.6 (GND), U1.12 (GND), U1.14 (GND), U1.26 (GND), U1.30 (GND), U1.53 (GND), U1.EGP (EXPOSED_GROUND), U2.1 (SDO/SA0), U2.2 (SDx), U2.3 (SCx), U2.6 (GND), U2.7 (GND), U3.4 (/CE), U3.5 (GND), U3.EP (THERMAL_PAD), U4.2 (SEL), U4.4 (CFG2), U4.8 (GND), U4.EP (THERMAL_PAD), U5.4 (IN/TRIG), U5.8 (GND), U6.2 (GND)
HAPTIC_EN: R_HAPTIC_EN.1, U1.1 (P0.13), U5.5 (EN)
HAPTIC_N: J3.2 (HAPTIC-), U5.9 (OUT-)
HAPTIC_P: J3.1 (HAPTIC+), U5.7 (OUT+)
HAPTIC_REG: C_HAPTIC_REG.1, U5.1 (REG)
I2C_SCL: R_I2C_SCL.2, U1.32 (P0.11), U2.13 (SCL), U5.2 (SCL)
I2C_SDA: R_I2C_SDA.2, U1.33 (P1.09), U2.14 (SDA), U5.3 (SDA)
IMU_INT1: U1.42 (P0.26), U2.4 (INT1)
LX1: L1.1, U4.9 (LX1)
LX2: L1.2, U4.7 (LX2)
RESET_N: TP5.1 (RESET_N), U1.19 (RESET_N)
R_CFG1_NODE: R_CFG1.1, U4.3 (CFG1)
R_CFG3_NODE: R_CFG3.1, U4.5 (CFG3)
R_ILIM_NODE: R_ILIM.1, U3.7 (ILIM/VSET)
R_ISET_NODE: R_ISET.1, U3.8 (ISET)
SWDCLK: TP4.1 (SWDCLK), U1.11 (SWDCLK)
SWDIO: TP3.1 (SWDIO), U1.15 (SWDIO)
SWO: TP6.1 (SWO), U1.8 (SWO)
SYS_RAIL: C_BUCK_IN.1, C_SYS.1, TP8.1 (SYS_RAIL), U3.1 (SYS), U4.1 (EN), U4.10 (VIN)
TP_IMU_INT2: TP7.1 (TP_IMU_INT2), U2.9 (INT2)
USB_CC1: J1.A5 (CC1), R_CC1.1
USB_CC2: J1.B5 (CC2), R_CC2.1
USB_DM_PROT: U1.55 (USB_DM), U6.4 (I/O2_PROT)
USB_DM_RAW: J1.A7 (D-), J1.B7 (D-), U6.3 (I/O2_RAW)
USB_DP_PROT: U1.54 (USB_DP), U6.6 (I/O1_PROT)
USB_DP_RAW: J1.A6 (D+), J1.B6 (D+), U6.1 (I/O1_RAW)
USB_SHIELD: J1.SH (SHIELD)
USB_VBUS_5V: C_CHG_IN.1, C_USB.1, F1.2, U1.31 (VBUS), U3.10 (IN), U6.5 (VBUS)
USB_VBUS_RAW: F1.1, J1.A4 (VBUS), J1.A9 (VBUS), J1.B4 (VBUS), J1.B9 (VBUS)

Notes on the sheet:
FACTORY REVIEW SOURCE Native gate status is recorded in controlled reports; fabricate only from a packaged PASS release.

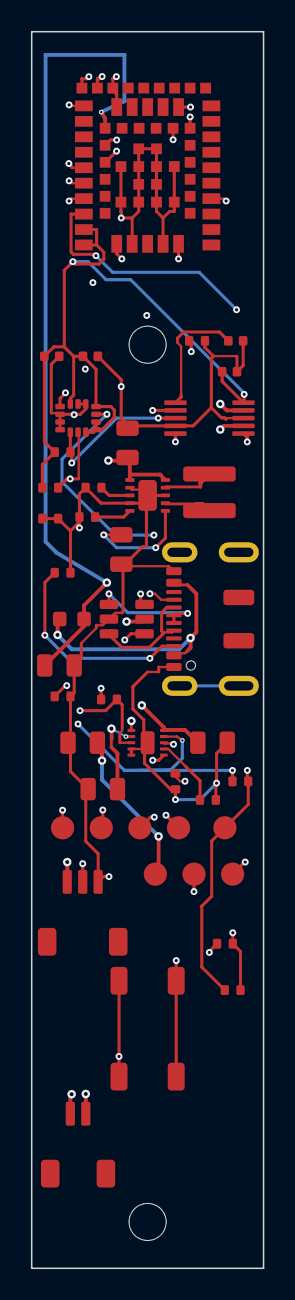
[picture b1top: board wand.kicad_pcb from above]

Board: 4 copper layers, 15.0 x 80.0 mm, 46 parts (0 on the bottom side), 35 nets.

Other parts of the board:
H1: MountingHole_2.4mm; wand_H1
H2: MountingHole_2.4mm; wand_H2

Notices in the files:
README.md:
项目采用 [MIT License](LICENSE)。SolidWorks 专有互操作程序集不会随仓库或默认发布包分发。
